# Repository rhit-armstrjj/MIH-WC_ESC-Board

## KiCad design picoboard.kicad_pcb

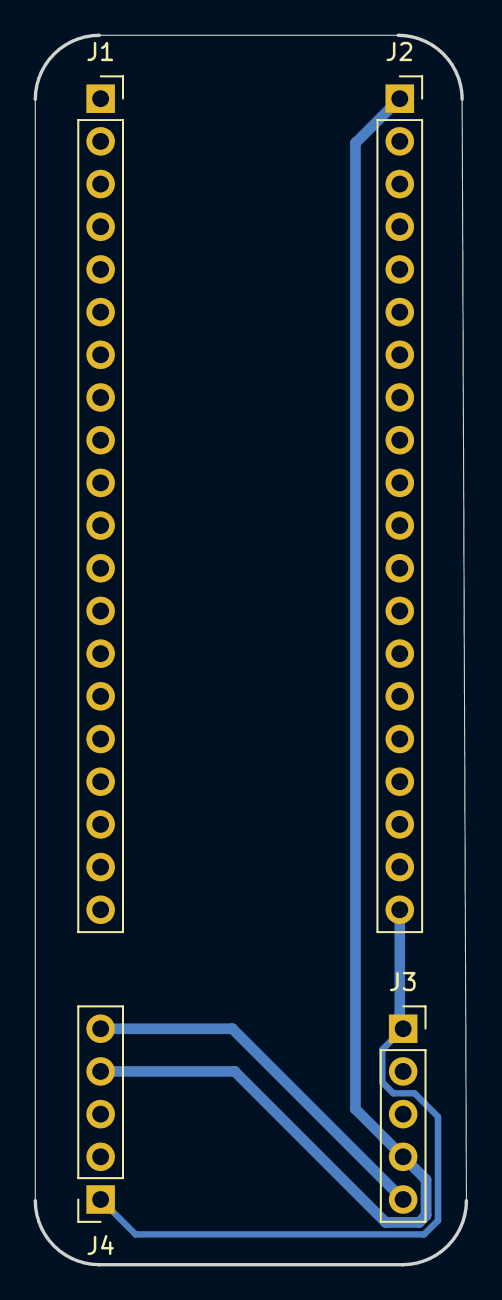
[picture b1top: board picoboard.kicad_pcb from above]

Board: 2 copper layers, 25.7 x 73.2 mm, 4 parts (0 on the bottom side), 3 nets.

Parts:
J1, J2: Conn_01x20; PinSocket_1x20_P2.54mm_Vertical
J3, J4: Conn_01x05; PinSocket_1x05_P2.54mm_Vertical

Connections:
+5V: J2.1, J3.4, J4.4
/A+: J2.20, J3.1, J4.1
GND: J2.3, J3.2, J3.5, J4.2, J4.5

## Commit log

2024-05-05 Picoboard
